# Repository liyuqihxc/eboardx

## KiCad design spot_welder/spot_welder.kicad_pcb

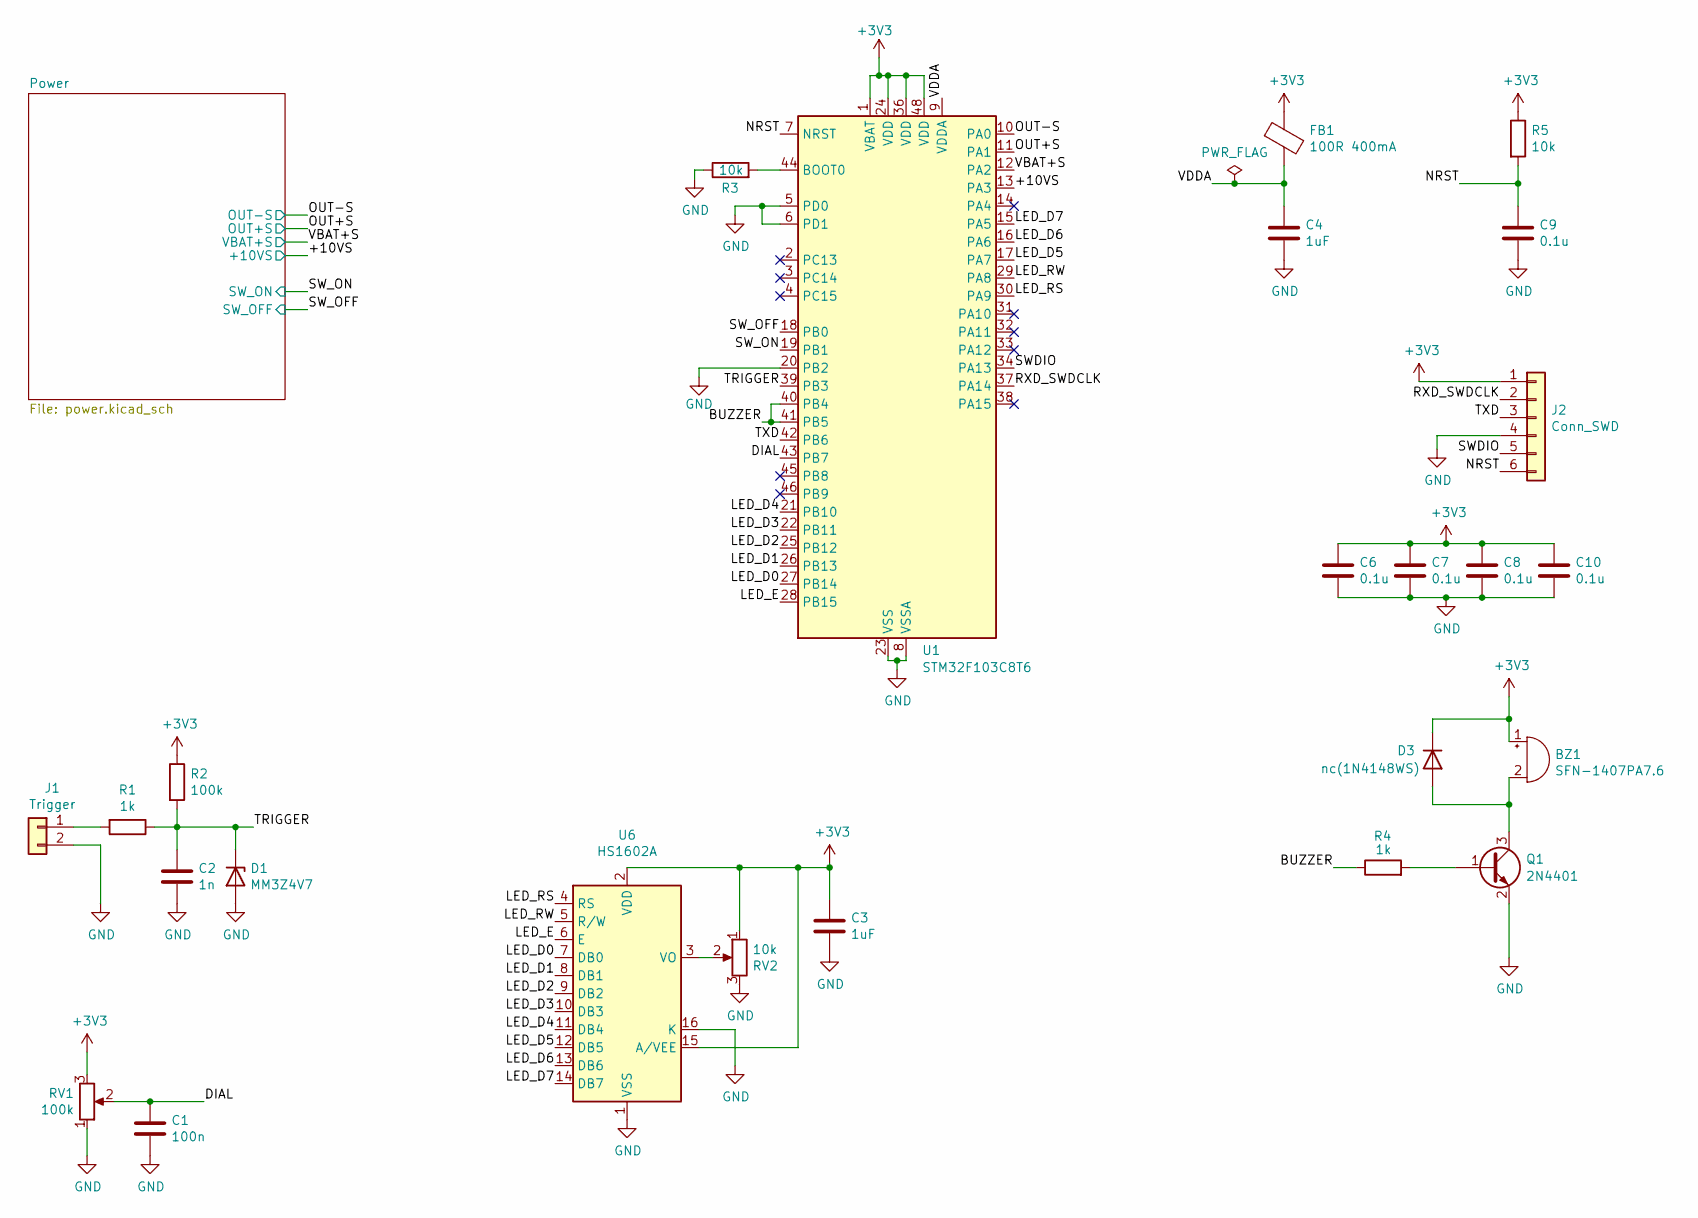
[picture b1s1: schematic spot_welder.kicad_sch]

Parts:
BZ1: SFN-1407PA7.6; Buzzer_15x7.5RM7.6; PartNo C360603
C1: 100n; C_0603_1608Metric
C2: 1n; C_0603_1608Metric
C3, C4: 1uF; C_0603_1608Metric
C6, C7, C8, C9, C10: 0.1u; C_0603_1608Metric
D1: MM3Z4V7; D_SOD-323; PartNo C2856973
D3: nc(1N4148WS); D_SOD-323; PartNo C2128
FB1: 100R 400mA; L_0603_1608Metric; PartNo C64181
J1: Trigger; PhoenixContact_MSTBVA_2,5_2-G_1x02_P5.00mm_Vertical; PartNo C395849
J2: Conn_SWD; PinHeader_1x06_P2.54mm_Vertical; PartNo DB126V-5.0-2P
Q1: 2N4401; SOT-23; PartNo C2145
R1, R4: 1k; R_0603_1608Metric
R2: 100k; R_0603_1608Metric
R3, R5: 10k; R_0603_1608Metric
RV1: 100k; Potentiometer_Bourns_3386C_Horizontal; PartNo C330448
RV2: 10k; Potentiometer_Bourns_3214J_Horizontal; PartNo C719176
U1: STM32F103C8T6; LQFP-48_7x7mm_P0.5mm; PartNo C8734
U6: HS1602A; PinSocket_1x16_P2.54mm_Vertical; PartNo C5329588

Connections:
+3V3: BZ1.1 (-), C3.1, C6.1, C7.1, C8.1, C10.1, D3.1 (K), FB1.1, J2.1, R2.1, R5.1, RV1.3, RV2.1, U1.1 (VBAT), U1.24 (VDD), U1.36 (VDD), U1.48 (VDD), U6.2 (VDD), U6.15 (A/VEE); also elsewhere on the board
/+10VS: U1.13 (PA3); also elsewhere on the board
/BUZZER: R4.1, U1.40 (PB4), U1.41 (PB5)
/DIAL: C1.1, RV1.2, U1.43 (PB7)
/LED_D0: U1.27 (PB14), U6.7 (DB0)
/LED_D1: U1.26 (PB13), U6.8 (DB1)
/LED_D2: U1.25 (PB12), U6.9 (DB2)
/LED_D3: U1.22 (PB11), U6.10 (DB3)
/LED_D4: U1.21 (PB10), U6.11 (DB4)
/LED_D5: U1.17 (PA7), U6.12 (DB5)
/LED_D6: U1.16 (PA6), U6.13 (DB6)
/LED_D7: U1.15 (PA5), U6.14 (DB7)
/LED_E: U1.28 (PB15), U6.6 (E)
/LED_RS: U1.30 (PA9), U6.4 (RS)
/LED_RW: U1.29 (PA8), U6.5 (R/W)
/NRST: C9.1, J2.6, R5.2, U1.7 (NRST)
/OUT+S: U1.11 (PA1); also elsewhere on the board
/OUT-S: U1.10 (PA0); also elsewhere on the board
/RXD_SWDCLK: J2.2, U1.37 (PA14)
/SWDIO: J2.5, U1.34 (PA13)
/SW_OFF: U1.18 (PB0); also elsewhere on the board
/SW_ON: U1.19 (PB1); also elsewhere on the board
/TRIGGER: C2.1, D1.1 (K), R1.1, R2.2, U1.39 (PB3)
/TXD: J2.3, U1.42 (PB6)
/VBAT+S: U1.12 (PA2); also elsewhere on the board
/VDDA: C4.1, FB1.2, U1.9 (VDDA)
unnamed: BZ1.2 (+), D3.2 (A), Q1.3 (C)
unnamed: J1.1, R1.2
unnamed: Q1.1 (B), R4.2
unnamed: R3.2, U1.44 (BOOT0)
unnamed: RV2.2, U6.3 (VO)
VBAT-: C1.2, C2.2, C3.2, C4.2, C6.2, C7.2, C8.2, C9.2, C10.2, D1.2 (A), J1.2, J2.4, Q1.2 (E), R3.1, RV1.1, RV2.3, U1.5 (PD0), U1.6 (PD1), U1.8 (VSSA), U1.20 (PB2), U1.23 (VSS), U1.35 (VSS), U1.47 (VSS), U6.1 (VSS), U6.16 (K); also elsewhere on the board

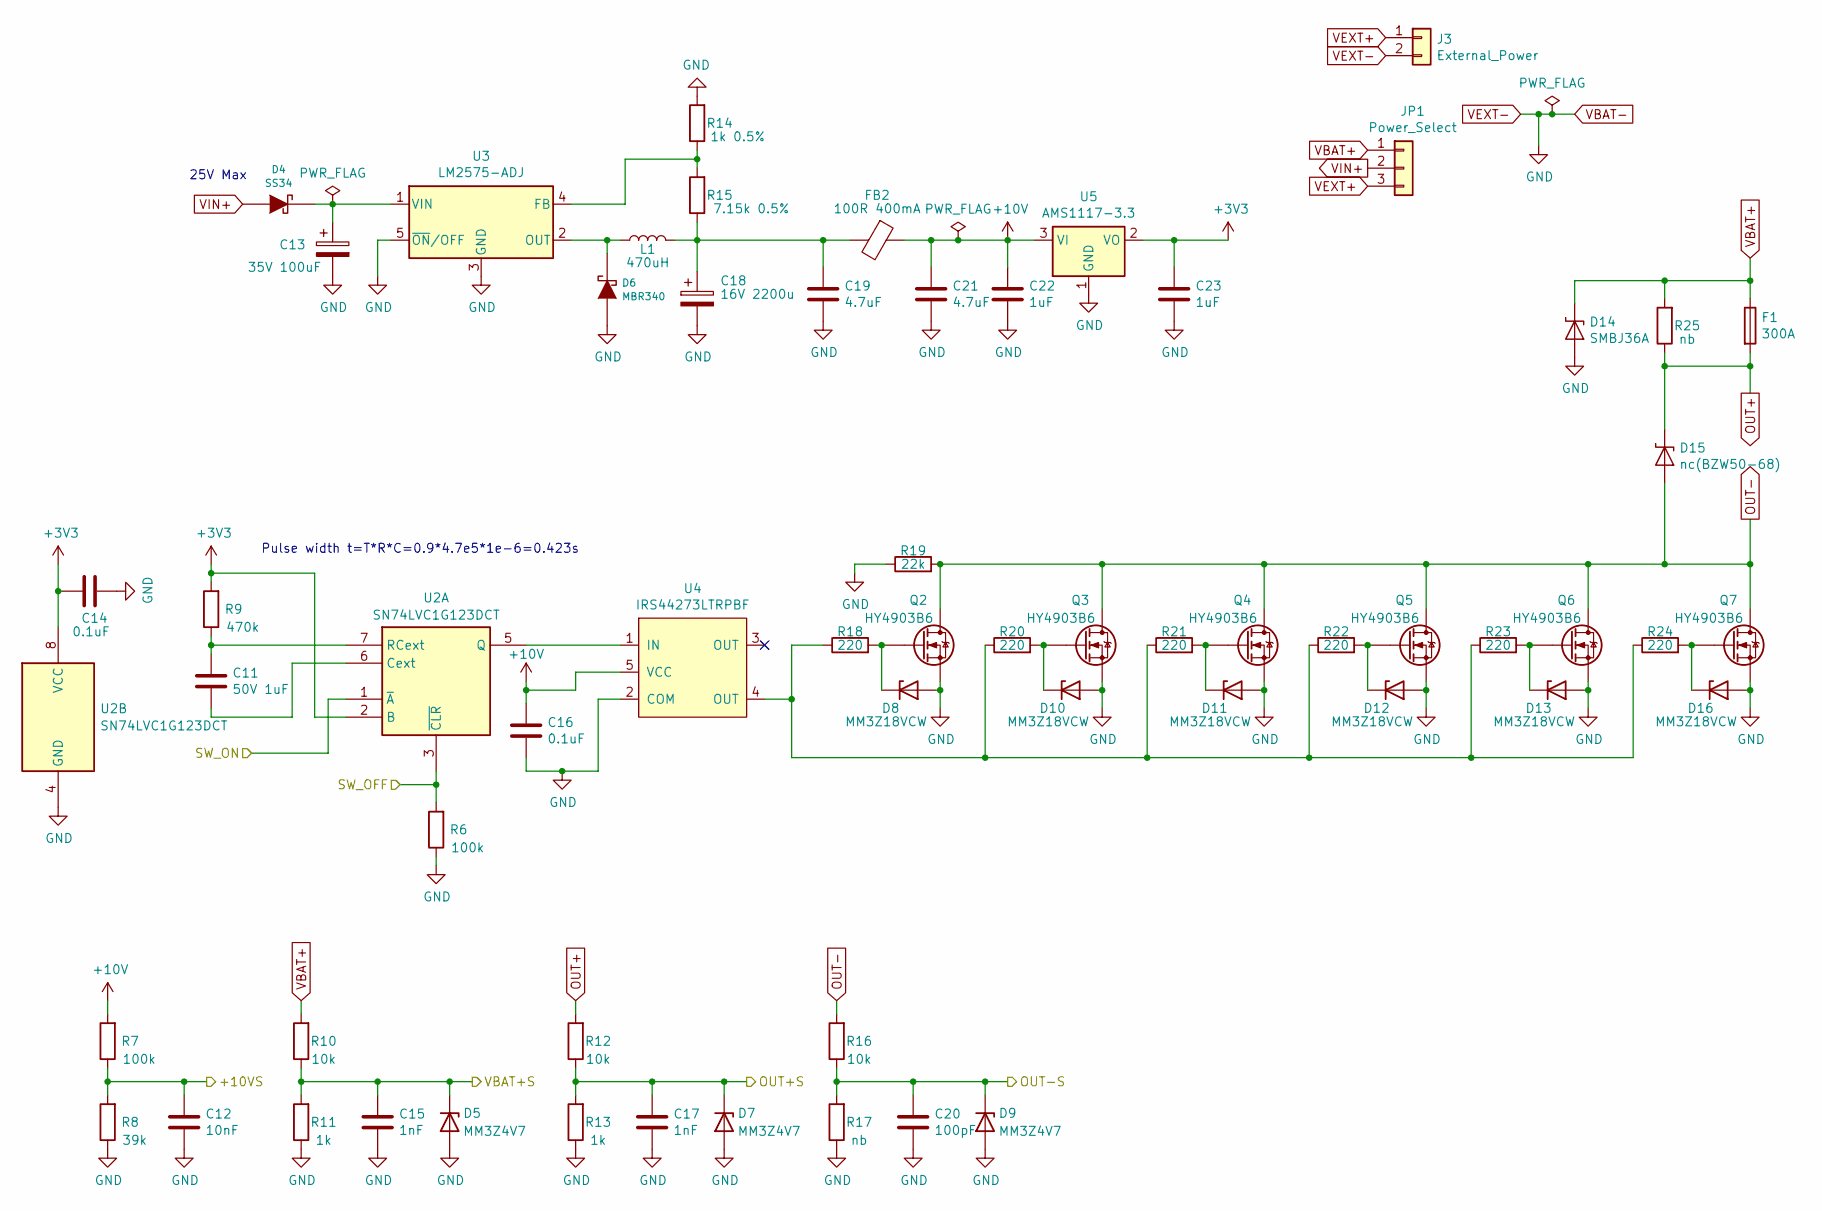
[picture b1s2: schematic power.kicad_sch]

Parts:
C11: 50V 1uF; C_0603_1608Metric
C12: 10nF; C_0603_1608Metric
C13: 35V 100uF; CP_Elec_6.3x7.7; PartNo C141427
C14, C16: 0.1uF; C_0603_1608Metric
C15, C17: 1nF; C_0603_1608Metric
C18: 16V 2200u; CP_Elec_16x17.5; PartNo C239248
C19, C21: 4.7uF; C_0603_1608Metric; PartNo C19666
C20: 100pF; C_0603_1608Metric
C22, C23: 1uF; C_0603_1608Metric
D4: SS34; D_SMA; PartNo C8678
D5, D7, D9: MM3Z4V7; D_SOD-323; PartNo C2856973
D6: MBR340; D_SOD-123F; PartNo C475721
D8, D10, D11, D12, D13, D16: MM3Z18VCW; D_SOD-323; PartNo C2926440
D14: SMBJ36A; D_SMB; PartNo C5331118
D15: nc(BZW50-68); D_P600_R-6_P7.62mm_Vertical_AnodeUp
F1: 300A; FUSE
FB2: 100R 400mA; L_0603_1608Metric; PartNo C64181
J3: External_Power; PhoenixContact_MSTBVA_2,5_2-G_1x02_P5.00mm_Vertical; PartNo C395849
JP1: Power_Select; PinHeader_1x03_P2.54mm_Vertical; PartNo C49257
L1: 470uH; L_12x12mm_H8mm; PartNo C10153
Q2, Q3, Q4, Q5, Q6, Q7: HY4903B6; TO-263-6; PartNo C133393
R6, R7: 100k; R_0603_1608Metric
R8: 39k; R_0603_1608Metric
R9: 470k; R_0603_1608Metric
R10, R12, R16: 10k; R_0603_1608Metric
R11, R13: 1k; R_0603_1608Metric
R14: 1k 0.5%; R_0603_1608Metric
R15: 7.15k 0.5%; R_0603_1608Metric
R17, R25: nb; R_0603_1608Metric
R18, R20, R21, R22, R23, R24: 220; R_0603_1608Metric
R19: 22k; R_0603_1608Metric
U2: SN74LVC1G123DCT; SSOP-8_2.95x2.8mm_P0.65mm; PartNo C123302
U3: LM2575-ADJ; TO-263-5_TabPin3; PartNo C347407
U4: IRS44273LTRPBF; SOT-23-5; PartNo C126909
U5: AMS1117-3.3; SOT-223-3_TabPin2; PartNo C5250992

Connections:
+3V3: C14.2, C23.1, R9.2, U2.2 (B), U2.8 (VCC), U5.2 (VO); also elsewhere on the board
+10V: C16.1, C21.1, C22.1, FB2.1, R7.2, U4.5 (VCC), U5.3 (VI)
/+10VS: C12.1, R7.1, R8.2; also elsewhere on the board
/OUT+S: C17.1, D7.1 (K), R12.1, R13.2; also elsewhere on the board
/OUT-S: C20.1, D9.1 (K), R16.1, R17.2; also elsewhere on the board
/SW_OFF: R6.2, U2.3 (~CLR); also elsewhere on the board
/SW_ON: U2.1 (~A); also elsewhere on the board
/VBAT+S: C15.1, D5.1 (K), R10.1, R11.2; also elsewhere on the board
unnamed: C18.1, C19.1, FB2.2, L1.2, R15.1
unnamed: C13.1, D4.2 (K), U3.1 (VIN)
unnamed: D6.2 (K), L1.1, U3.2 (OUT)
unnamed: D8.1 (K), Q2.1 (G), R18.2
unnamed: D10.1 (K), Q3.1 (G), R20.2
unnamed: D11.1 (K), Q4.1 (G), R21.2
unnamed: D12.1 (K), Q5.1 (G), R22.2
unnamed: D13.1 (K), Q6.1 (G), R23.2
unnamed: D16.1 (K), Q7.1 (G), R24.2
unnamed: R18.1, R20.1, R21.1, R22.1, R23.1, R24.1, U4.4 (OUT)
unnamed: C11.2, U2.6 (Cext)
unnamed: U2.5 (Q), U4.1 (IN)
unnamed: C11.1, R9.1, U2.7 (RCext)
unnamed: R14.1, R15.2, U3.4 (FB)
OUT+: D15.1 (A1), F1.2, R12.2, R25.1
OUT-: D15.2 (A2), Q2.4 (D), Q3.4 (D), Q4.4 (D), Q5.4 (D), Q6.4 (D), Q7.4 (D), R16.2, R19.2
VBAT+: D14.1 (A1), F1.1, JP1.1, R10.2, R25.2
VBAT-: C12.2, C13.2, C14.1, C15.2, C16.2, C17.2, C18.2, C19.2, C20.2, C21.2, C22.2, C23.2, D5.2 (A), D6.1 (A), D7.2 (A), D8.2 (A), D9.2 (A), D10.2 (A), D11.2 (A), D12.2 (A), D13.2 (A), D14.2 (A2), D16.2 (A), J3.2, Q2.2 (S), Q2.3 (S), Q2.5 (S), Q2.6 (S), Q2.7 (S), Q3.2 (S), Q3.3 (S), Q3.5 (S), Q3.6 (S), Q3.7 (S), Q4.2 (S), Q4.3 (S), Q4.5 (S), Q4.6 (S), Q4.7 (S), Q5.2 (S), Q5.3 (S), Q5.5 (S), Q5.6 (S), Q5.7 (S), Q6.2 (S), Q6.3 (S), Q6.5 (S), Q6.6 (S), Q6.7 (S), Q7.2 (S), Q7.3 (S), Q7.5 (S), Q7.6 (S), Q7.7 (S), R6.1, R8.1, R11.1, R13.1, R14.2, R17.1, R19.1, U2.4 (GND), U3.3 (GND), U3.5 (~ON/OFF), U4.2 (COM), U5.1 (GND); also elsewhere on the board
VEXT+: J3.1, JP1.3
VIN+: D4.1 (A), JP1.2

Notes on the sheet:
25V Max
Pulse width t=T*R*C=0.9*4.7e5*1e-6=0.423s

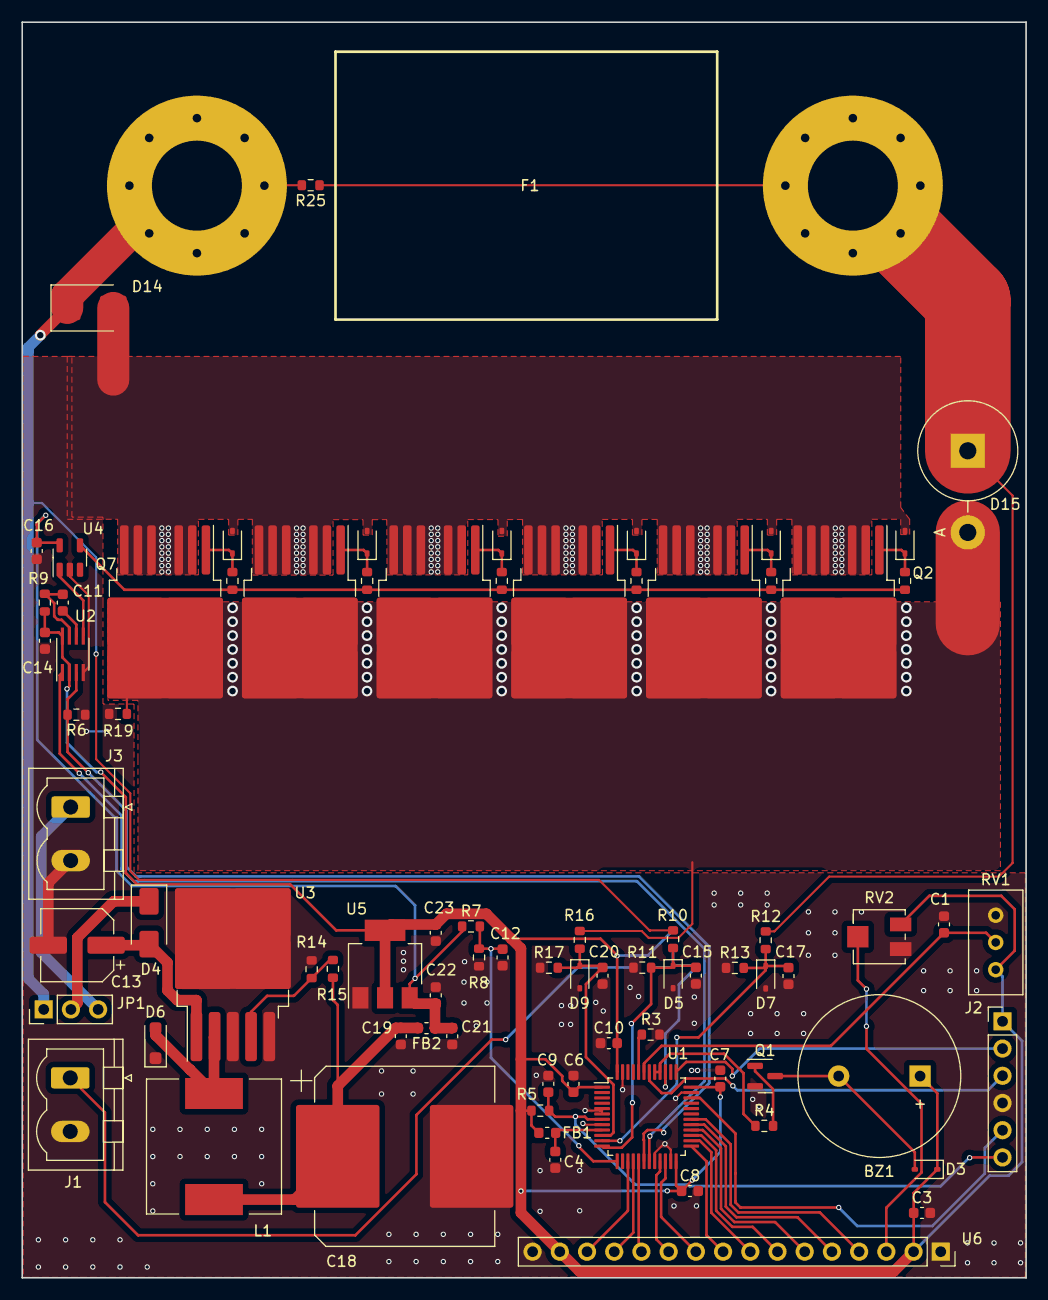
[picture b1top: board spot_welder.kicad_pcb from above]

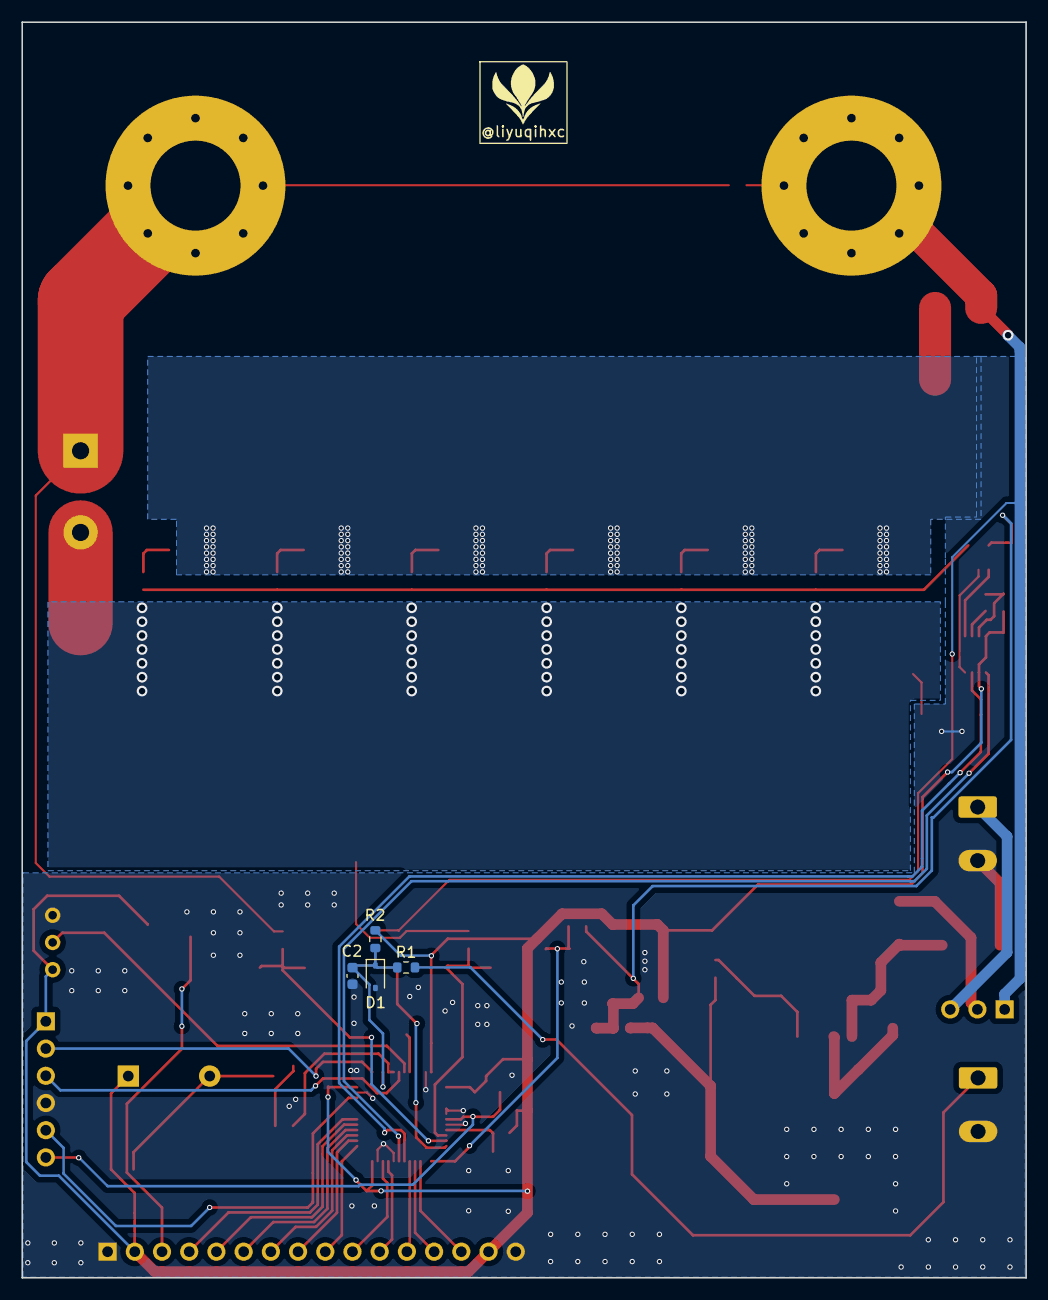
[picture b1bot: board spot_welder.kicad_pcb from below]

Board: 2 copper layers, 93.7 x 117.2 mm, 86 parts (4 on the bottom side), 52 nets.

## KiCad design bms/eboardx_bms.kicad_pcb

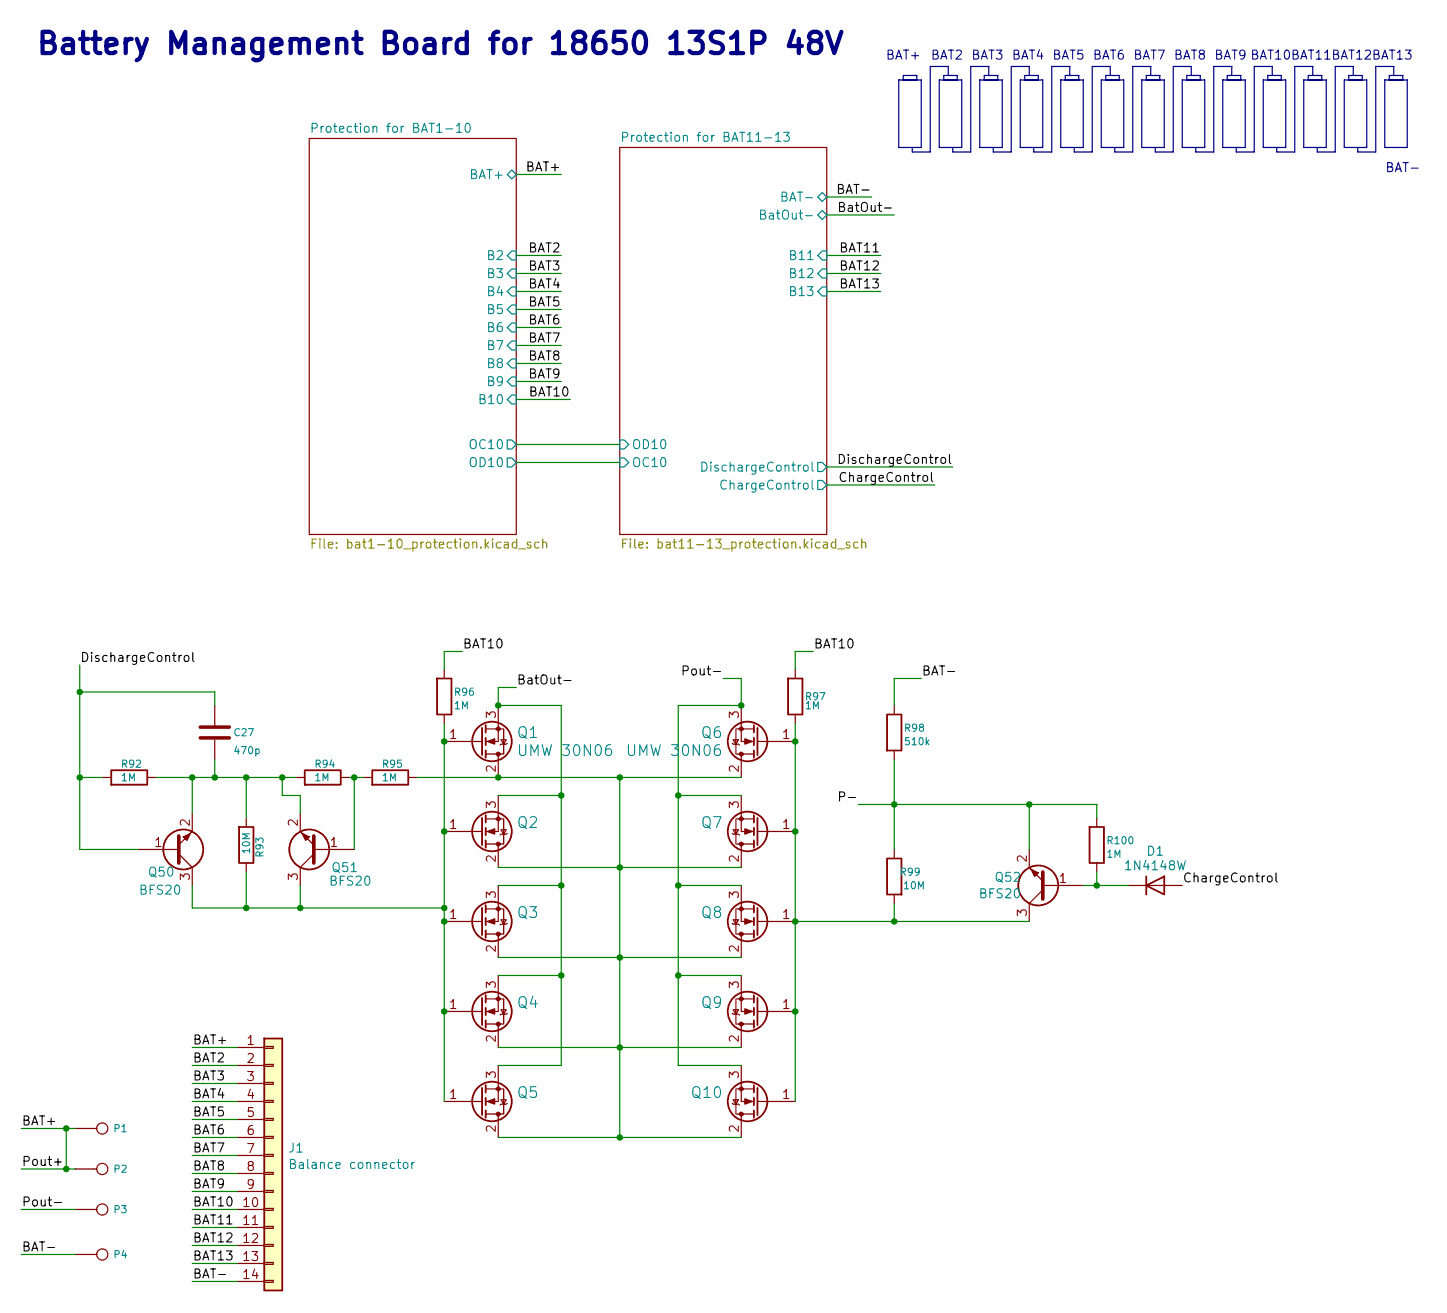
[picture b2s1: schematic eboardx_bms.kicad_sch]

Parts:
C27: 470p; C_0603_1608Metric
D1: 1N4148W; D_SOD-123
J1: Balance connector; JST_PH_B14B-PH-K_1x14_P2.00mm_Vertical
P1: BAT+; 1PAD_4x5mm
P2: P+; 1PAD_4x5mm
P3: P-; 1PAD_4x5mm
P4: BAT-; 1PAD_4x5mm
Q1, Q2, Q3, Q4, Q5, Q6, Q7, Q8, Q9, Q10: UMW 30N06; TO-252-2
Q50, Q51, Q52: BFS20; SOT-23
R92, R94, R95, R96, R97, R100: 1M; R_0603_1608Metric
R93, R99: 10M; R_0603_1608Metric
R98: 510k; R_0603_1608Metric

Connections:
/BAT2: J1.2; also elsewhere on the board
/BAT3: J1.3; also elsewhere on the board
/BAT4: J1.4; also elsewhere on the board
/BAT5: J1.5; also elsewhere on the board
/BAT6: J1.6; also elsewhere on the board
/BAT7: J1.7; also elsewhere on the board
/BAT8: J1.8; also elsewhere on the board
/BAT9: J1.9; also elsewhere on the board
/BAT10: J1.10, R96.2, R97.2; also elsewhere on the board
/BAT11: J1.11; also elsewhere on the board
/BAT12: J1.12; also elsewhere on the board
/BAT13: J1.13; also elsewhere on the board
/BAT+: J1.1, P1.1, P2.1; also elsewhere on the board
/BAT-: J1.14, P4.1, R98.1; also elsewhere on the board
/BatOut-: Q1.3 (S), Q2.3 (S), Q3.3 (S), Q4.3 (S), Q5.3 (S); also elsewhere on the board
/ChargeControl: D1.2 (A); also elsewhere on the board
/DischargeControl: C27.2, Q50.1 (B), R92.2; also elsewhere on the board
/P-: Q52.2 (E), R98.2, R99.1, R100.2
/Pout-: P3.1, Q6.3 (S), Q7.3 (S), Q8.3 (S), Q9.3 (S), Q10.3 (S)
unnamed: D1.1 (K), Q52.1 (B), R100.1
unnamed: Q1.2 (D), Q2.2 (D), Q3.2 (D), Q4.2 (D), Q5.2 (D), Q6.2 (D), Q7.2 (D), Q8.2 (D), Q9.2 (D), Q10.2 (D), R95.1
unnamed: Q1.1 (G), Q2.1 (G), Q3.1 (G), Q4.1 (G), Q5.1 (G), Q50.3 (C), Q51.3 (C), R93.1, R96.1
unnamed: Q6.1 (G), Q7.1 (G), Q8.1 (G), Q9.1 (G), Q10.1 (G), Q52.3 (C), R97.1, R99.2
unnamed: C27.1, Q50.2 (E), Q51.2 (E), R92.1, R93.2, R94.2
unnamed: Q51.1 (B), R94.1, R95.2

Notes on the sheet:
BAT10
BAT9
BAT7
BAT11
BAT12
BAT8
BAT+
BAT2
BAT5
BAT3
BAT4
Battery Management Board for 18650 13S1P 48V
BAT13
BAT6
BAT-

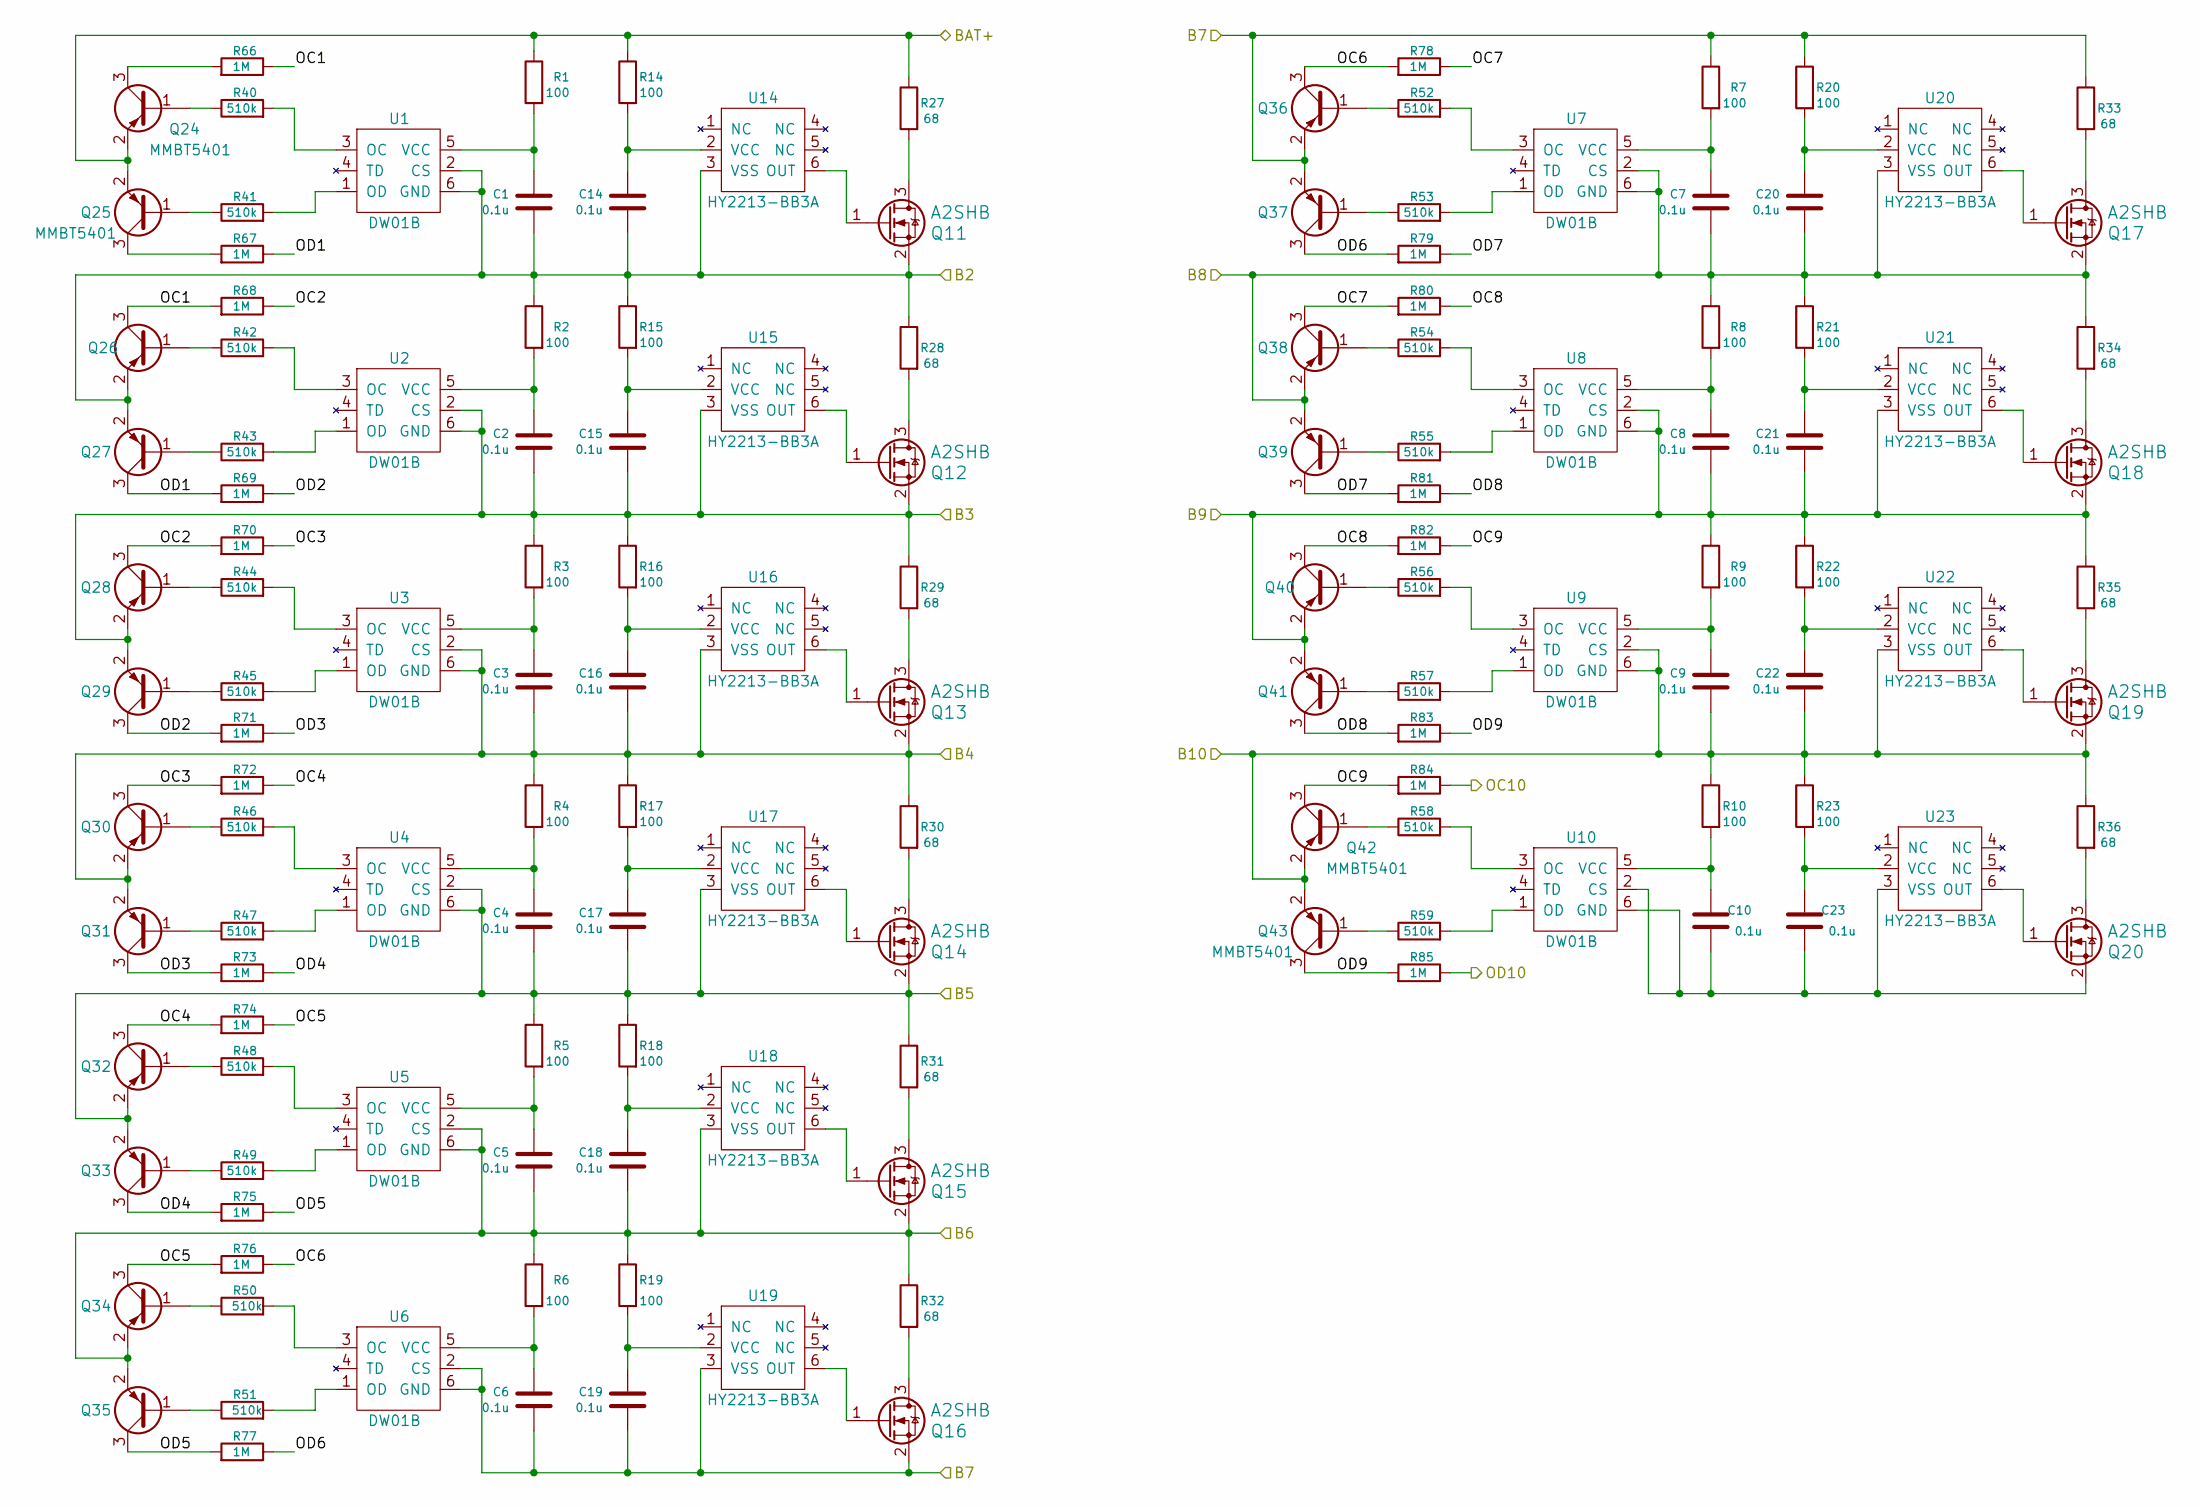
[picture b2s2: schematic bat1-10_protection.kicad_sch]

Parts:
C1, C2, C3, C4, C5, C6, C7, C8, C9, C10, C14, C15, C16, C17, C18, C19, C20, C21, C22, C23: 0.1u; C_0603_1608Metric
Q11, Q12, Q13, Q14, Q15, Q16, Q17, Q18, Q19, Q20: A2SHB; SOT-23
Q24, Q25, Q26, Q27, Q28, Q29, Q30, Q31, Q32, Q33, Q34, Q35, Q36, Q37, Q38, Q39, Q40, Q41, Q42, Q43: MMBT5401; SOT-23
R1, R2, R3, R4, R5, R6, R7, R8, R9, R10, R14, R15, R16, R17, R18, R19, R20, R21, R22, R23: 100; R_0603_1608Metric
R27, R28, R29, R30, R31, R32, R33, R34, R35, R36: 68; R_2512_6332Metric
R40, R41, R42, R43, R44, R45, R46, R47, R48, R49, R50, R51, R52, R53, R54, R55, R56, R57, R58, R59: 510k; R_0603_1608Metric
R66, R67, R68, R69, R70, R71, R72, R73, R74, R75, R76, R77, R78, R79, R80, R81, R82, R83, R84, R85: 1M; R_0603_1608Metric
U1, U2, U3, U4, U5, U6, U7, U8, U9, U10: DW01B; SOT-23-6
U14, U15, U16, U17, U18, U19, U20, U21, U22, U23: HY2213-BB3A; SOT-23-6

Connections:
/BAT2: C1.2, C14.2, Q11.2 (S), Q26.2 (E), Q27.2 (E), R2.1, R15.1, R28.1, U1.2 (CS), U1.6 (GND), U14.3 (VSS); also elsewhere on the board
/BAT3: C2.2, C15.2, Q12.2 (S), Q28.2 (E), Q29.2 (E), R3.1, R16.1, R29.1, U2.2 (CS), U2.6 (GND), U15.3 (VSS); also elsewhere on the board
/BAT4: C3.2, C16.2, Q13.2 (S), Q30.2 (E), Q31.2 (E), R4.1, R17.1, R30.1, U3.2 (CS), U3.6 (GND), U16.3 (VSS); also elsewhere on the board
/BAT5: C4.2, C17.2, Q14.2 (S), Q32.2 (E), Q33.2 (E), R5.1, R18.1, R31.1, U4.2 (CS), U4.6 (GND), U17.3 (VSS); also elsewhere on the board
/BAT6: C5.2, C18.2, Q15.2 (S), Q34.2 (E), Q35.2 (E), R6.1, R19.1, R32.1, U5.2 (CS), U5.6 (GND), U18.3 (VSS); also elsewhere on the board
/BAT7: C6.2, C19.2, Q16.2 (S), Q36.2 (E), Q37.2 (E), R7.1, R20.1, R33.1, U6.2 (CS), U6.6 (GND), U19.3 (VSS); also elsewhere on the board
/BAT8: C7.2, C20.2, Q17.2 (S), Q38.2 (E), Q39.2 (E), R8.1, R21.1, R34.1, U7.2 (CS), U7.6 (GND), U20.3 (VSS); also elsewhere on the board
/BAT9: C8.2, C21.2, Q18.2 (S), Q40.2 (E), Q41.2 (E), R9.1, R22.1, R35.1, U8.2 (CS), U8.6 (GND), U21.3 (VSS); also elsewhere on the board
/BAT10: C9.2, C22.2, Q19.2 (S), Q42.2 (E), Q43.2 (E), R10.1, R23.1, R36.1, U9.2 (CS), U9.6 (GND), U22.3 (VSS); also elsewhere on the board
/BAT+: Q24.2 (E), Q25.2 (E), R1.1, R14.1, R27.1; also elsewhere on the board
/Protection for BAT1-10/OC1: Q26.3 (C), R66.1, R68.2
/Protection for BAT1-10/OC2: Q28.3 (C), R68.1, R70.2
/Protection for BAT1-10/OC3: Q30.3 (C), R70.1, R72.2
/Protection for BAT1-10/OC4: Q32.3 (C), R72.1, R74.2
/Protection for BAT1-10/OC5: Q34.3 (C), R74.1, R76.2
/Protection for BAT1-10/OC6: Q36.3 (C), R76.1, R78.2
/Protection for BAT1-10/OC7: Q38.3 (C), R78.1, R80.2
/Protection for BAT1-10/OC8: Q40.3 (C), R80.1, R82.2
/Protection for BAT1-10/OC9: Q42.3 (C), R82.1, R84.2
/Protection for BAT1-10/OC10: R84.1; also elsewhere on the board
/Protection for BAT1-10/OD1: Q27.3 (C), R67.1, R69.2
/Protection for BAT1-10/OD2: Q29.3 (C), R69.1, R71.2
/Protection for BAT1-10/OD3: Q31.3 (C), R71.1, R73.2
/Protection for BAT1-10/OD4: Q33.3 (C), R73.1, R75.2
/Protection for BAT1-10/OD5: Q35.3 (C), R75.1, R77.2
/Protection for BAT1-10/OD6: Q37.3 (C), R77.1, R79.2
/Protection for BAT1-10/OD7: Q39.3 (C), R79.1, R81.2
/Protection for BAT1-10/OD8: Q41.3 (C), R81.1, R83.2
/Protection for BAT1-10/OD9: Q43.3 (C), R83.1, R85.2
/Protection for BAT1-10/OD10: R85.1; also elsewhere on the board
unnamed: Q11.3 (D), R27.2
unnamed: Q11.1 (G), U14.6 (OUT)
unnamed: Q12.3 (D), R28.2
unnamed: Q12.1 (G), U15.6 (OUT)
unnamed: Q13.3 (D), R29.2
unnamed: Q13.1 (G), U16.6 (OUT)
unnamed: Q14.3 (D), R30.2
unnamed: Q14.1 (G), U17.6 (OUT)
unnamed: Q15.3 (D), R31.2
unnamed: Q15.1 (G), U18.6 (OUT)
unnamed: Q16.3 (D), R32.2
unnamed: Q16.1 (G), U19.6 (OUT)
unnamed: Q17.3 (D), R33.2
unnamed: Q17.1 (G), U20.6 (OUT)
unnamed: Q18.3 (D), R34.2
unnamed: Q18.1 (G), U21.6 (OUT)
unnamed: Q19.3 (D), R35.2
unnamed: Q19.1 (G), U22.6 (OUT)
unnamed: Q20.3 (D), R36.2
unnamed: Q20.1 (G), U23.6 (OUT)
unnamed: C10.2, C23.2, Q20.2 (S), U10.2 (CS), U10.6 (GND), U23.3 (VSS)
unnamed: Q24.1 (B), R40.1
unnamed: Q24.3 (C), R66.2
unnamed: Q25.1 (B), R41.1
unnamed: Q25.3 (C), R67.2
unnamed: Q26.1 (B), R42.1
unnamed: Q27.1 (B), R43.1
unnamed: Q28.1 (B), R44.1
unnamed: Q29.1 (B), R45.1
unnamed: Q30.1 (B), R46.1
unnamed: Q31.1 (B), R47.1
unnamed: Q32.1 (B), R48.1
unnamed: Q33.1 (B), R49.1
unnamed: Q34.1 (B), R50.1
unnamed: Q35.1 (B), R51.1
unnamed: Q36.1 (B), R52.1
unnamed: Q37.1 (B), R53.1
unnamed: Q38.1 (B), R54.1
unnamed: Q39.1 (B), R55.1
unnamed: Q40.1 (B), R56.1
unnamed: Q41.1 (B), R57.1
unnamed: Q42.1 (B), R58.1
unnamed: Q43.1 (B), R59.1
unnamed: R40.2, U1.3 (OC)
unnamed: R41.2, U1.1 (OD)
unnamed: C1.1, R1.2, U1.5 (VCC)
unnamed: R42.2, U2.3 (OC)
unnamed: R43.2, U2.1 (OD)
unnamed: C2.1, R2.2, U2.5 (VCC)
unnamed: R44.2, U3.3 (OC)
unnamed: R45.2, U3.1 (OD)
unnamed: C3.1, R3.2, U3.5 (VCC)
unnamed: R46.2, U4.3 (OC)
unnamed: R47.2, U4.1 (OD)
unnamed: C4.1, R4.2, U4.5 (VCC)
unnamed: R48.2, U5.3 (OC)
unnamed: R49.2, U5.1 (OD)
unnamed: C5.1, R5.2, U5.5 (VCC)
unnamed: R50.2, U6.3 (OC)
unnamed: R51.2, U6.1 (OD)
unnamed: C6.1, R6.2, U6.5 (VCC)
unnamed: R52.2, U7.3 (OC)
unnamed: R53.2, U7.1 (OD)
unnamed: C7.1, R7.2, U7.5 (VCC)
unnamed: R54.2, U8.3 (OC)
unnamed: R55.2, U8.1 (OD)
unnamed: C8.1, R8.2, U8.5 (VCC)
unnamed: R56.2, U9.3 (OC)
unnamed: R57.2, U9.1 (OD)
unnamed: C9.1, R9.2, U9.5 (VCC)
unnamed: R58.2, U10.3 (OC)
unnamed: R59.2, U10.1 (OD)
unnamed: C10.1, R10.2, U10.5 (VCC)
unnamed: C14.1, R14.2, U14.2 (VCC)
unnamed: C15.1, R15.2, U15.2 (VCC)
unnamed: C16.1, R16.2, U16.2 (VCC)
unnamed: C17.1, R17.2, U17.2 (VCC)
unnamed: C18.1, R18.2, U18.2 (VCC)
unnamed: C19.1, R19.2, U19.2 (VCC)
unnamed: C20.1, R20.2, U20.2 (VCC)
unnamed: C21.1, R21.2, U21.2 (VCC)
unnamed: C22.1, R22.2, U22.2 (VCC)
unnamed: C23.1, R23.2, U23.2 (VCC)
